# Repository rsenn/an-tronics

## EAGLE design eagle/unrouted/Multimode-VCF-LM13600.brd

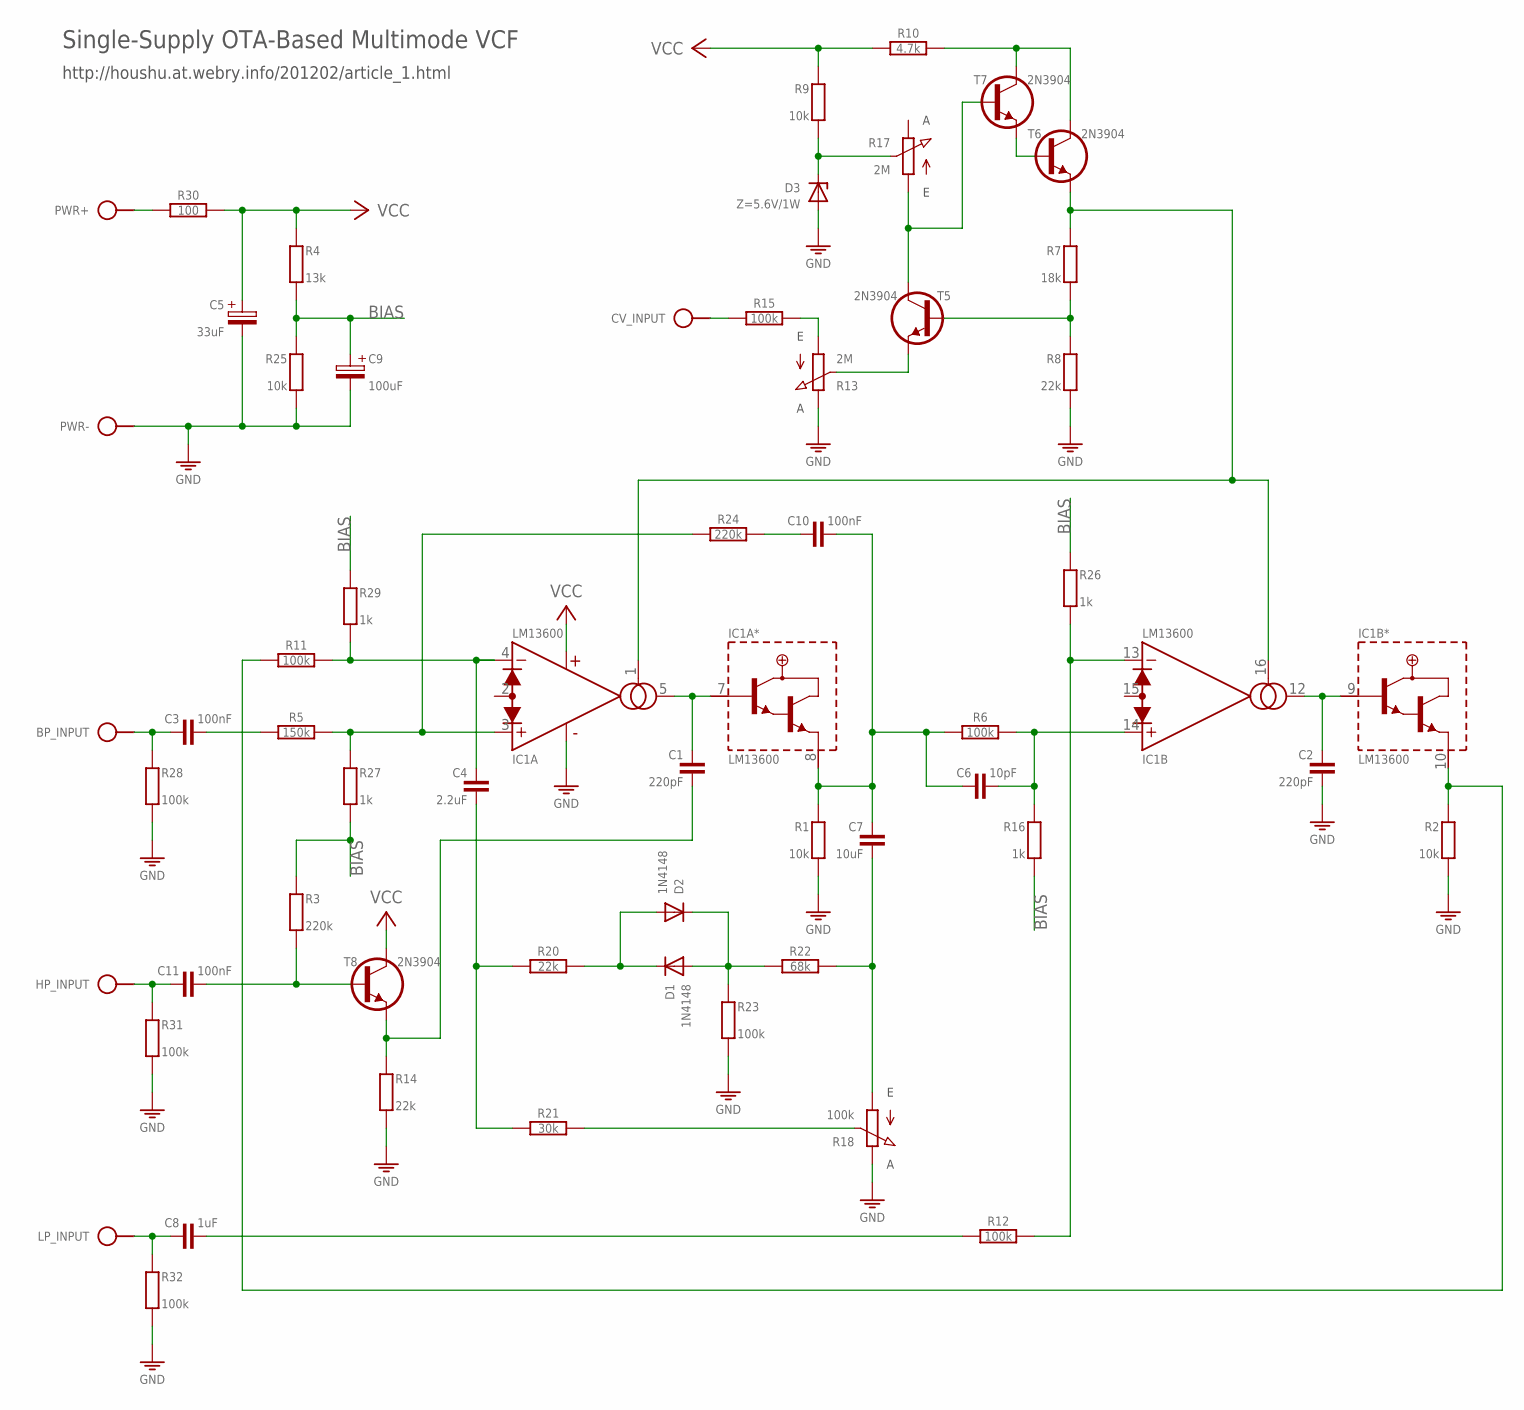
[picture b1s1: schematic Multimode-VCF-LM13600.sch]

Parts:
BP_INPUT: SPAD
C1, C2: 220pF; C050-020X036/V
C3, C10: 100nF; C050-020X044
C4: 2.2uF; C050-024X044/V
C5: 33uF; E2.5-4/V
C6: 10pF; C050-020X036
C7: 10uF; C050-020X036/V
C8: 1uF; C050-024X044
C9: 100uF; E2.5-4/V
C11: 100nF; C050-020X044/V
CV_INPUT: SPAD
D1: 1N4148; DO34-2,5-A
D2: 1N4148; DO34-2,5
D3: Z=5.6V/1W; DO35Z7/V
HP_INPUT: SPAD
IC1: LM13600; DIL16
LP_INPUT: SPAD
PWR: SPAD+--+; SPAD-+
R1, R9, R25: 10k; 0204/10-V
R2: 10k; 0204/10
R3, R24: 220k; 0204/10-V
R4: 13k; 0204/10-V
R5: 150k; 0204/10
R6: 100k; 0204/7-V
R7: 18k; 0204/10-V
R8, R14: 22k; 0204/10-V
R10: 4.7k; 0204/10
R11, R12, R15: 100k; 0204/10
R13, R17: 2M; POT-V
R16: 1k; 0204/7-V
R18: 100k; POT
R20: 22k; 0204/10
R21: 30k; 0204/10
R22: 68k; 0204/10
R23, R28, R31, R32: 100k; 0204/10-V
R26: 1k; 0204/7
R27, R29: 1k; 0204/10-V
R30: 100; 0204/10
T5, T6, T7, T8: 2N3904; TO92

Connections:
BIAS: C9.+, R3.1, R4.2, R16.1 (2), R25.1, R26.2 (1), R27.2, R29.1
GND: C2.2, C5.-, C9.-, D3.A, IC1.6 (V-), PWR.1, R1.2, R2.1 (2), R8.2, R13.E, R14.2, R18.3 (E), R23.2, R25.2, R28.2, R31.2, R32.2
unnamed: C4.2, R20.1, R21.1
unnamed: IC1.3 (+IN), R5.2, R24.1, R27.1
unnamed: C1.2, R14.1, T8.1 (E)
unnamed: C11.2, R3.2, T8.2 (B)
unnamed: C1.1, IC1.5 (OUT), IC1.7 (BUFF/IN)
unnamed: C6.1, C7.1, C10.2, IC1.8 (BUFF/OUT), R1.1, R6.1
unnamed: D1.C, D2.A, R20.2
unnamed: D1.A, D2.C, R22.1, R23.1
unnamed: C10.1, R24.2
unnamed: C6.2, IC1.14 (+IN), R6.2, R16.2 (1)
unnamed: R18.2 (S), R21.2
unnamed: C7.2, R18.1 (A), R22.2
unnamed: C4.1, IC1.4 (-IN), R11.2, R29.2
unnamed: IC1.13 (-IN), R12.2, R26.1 (2)
unnamed: C8.2, R12.1
unnamed: C8.1, LP_INPUT.1, R32.1
unnamed: C11.1, HP_INPUT.1, R31.1
unnamed: C3.2, R5.1
unnamed: BP_INPUT.1, C3.1, R28.1
unnamed: C2.1, IC1.9 (BUFF/IN), IC1.12 (OUT)
unnamed: IC1.10 (BUFF/OUT), R2.2 (1), R11.1
unnamed: R17.A, T5.3 (C), T7.2 (B)
unnamed: T6.2 (B), T7.1 (E)
unnamed: IC1.1 (AMP/BIAS), IC1.16 (AMP/BIAS), R7.1, T6.1 (E)
unnamed: R7.2, R8.1, T5.2 (B)
unnamed: D3.C, R9.2, R17.S
unnamed: R10.2, T6.3 (C), T7.3 (C)
unnamed: R13.S, T5.1 (E)
unnamed: CV_INPUT.1, R15.1
unnamed: R13.A, R15.2
unnamed: PWR.2, R30.1
VCC: C5.+, IC1.11 (V+), R4.1, R9.1, R10.1, R30.2, T8.3 (C)

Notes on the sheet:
http://houshu.at.webry.info/201202/article_1.html
Single-Supply OTA-Based Multimode VCF

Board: 2 copper layers, 55 parts (0 on the bottom side), 34 nets, no tracks yet.

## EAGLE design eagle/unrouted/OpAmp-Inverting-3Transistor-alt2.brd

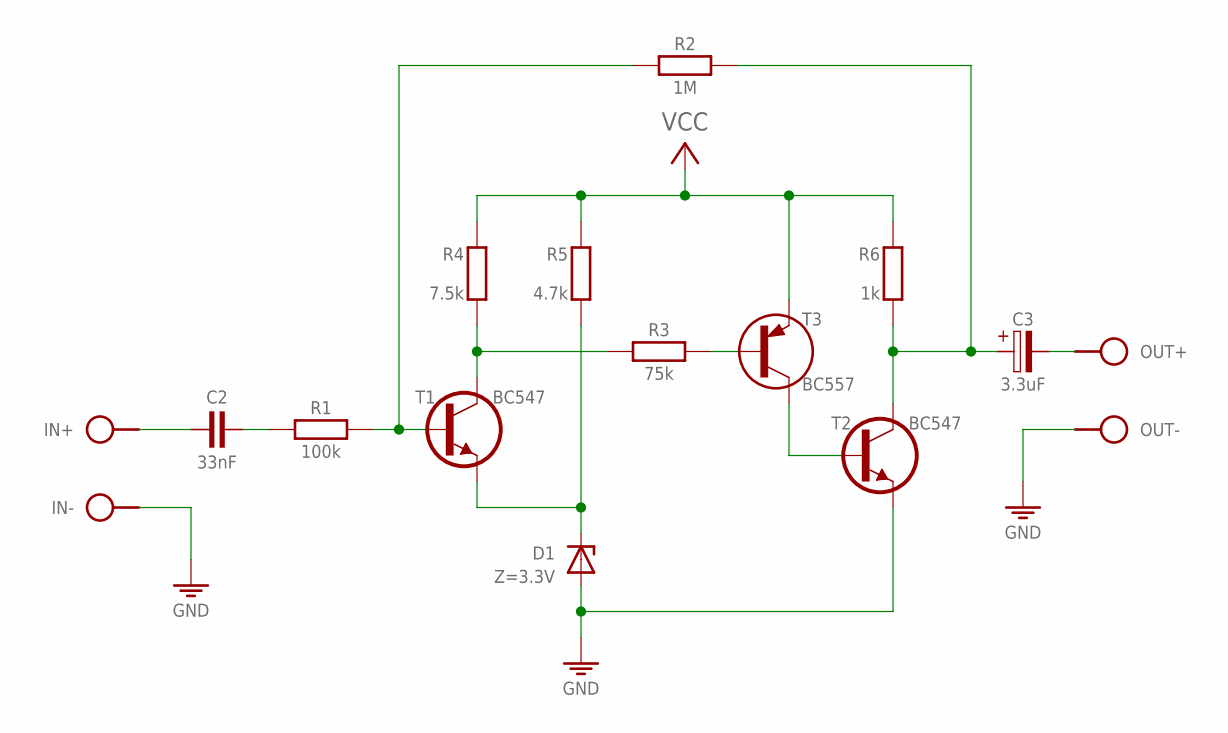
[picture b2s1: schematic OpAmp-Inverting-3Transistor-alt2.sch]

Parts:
C2: 33nF; C050-020X044
C3: 3.3uF; E2.5-4/V
D1: Z=3.3V; DO34Z2,5
IN: SPAD+--+; SPAD-+
J1: VCC_GNDPWR-R; PWR-R
OUT: SPAD+-+-; SPAD+-
R1: 100k; 0202/10-V
R2: 1M; 0202/7
R3: 75k; 0202/7
R4: 7.5k; 0202/7
R5: 4.7k; 0202/7
R6: 1k; 0202/7-V
T1, T2: BC547; TO92-CBE
T3: BC557; TO92-CBE

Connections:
GND: D1.A, IN.1, J1.1 (GND), OUT.1, T2.E
unnamed: D1.C, R5.1 (2), T1.E
unnamed: R3.1, R4.1 (2), T1.C
unnamed: T2.B, T3.C
unnamed: C2.2, IN.2
unnamed: C2.1, R1.1
unnamed: R1.2, R2.1, T1.B
unnamed: R3.2, T3.B
unnamed: C3.+, R2.2, R6.1 (2), T2.C
unnamed: C3.-, OUT.2
VCC: J1.2 (VCC), R4.2 (1), R5.2 (1), R6.2 (1), T3.E

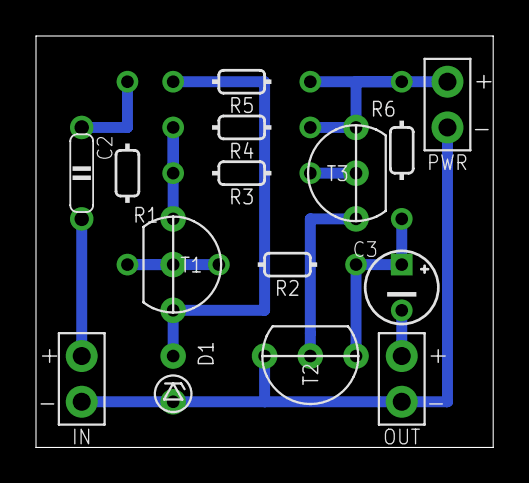
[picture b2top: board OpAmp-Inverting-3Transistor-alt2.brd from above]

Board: 2 copper layers, 25.4 x 22.9 mm, 15 parts (0 on the bottom side), 11 nets.

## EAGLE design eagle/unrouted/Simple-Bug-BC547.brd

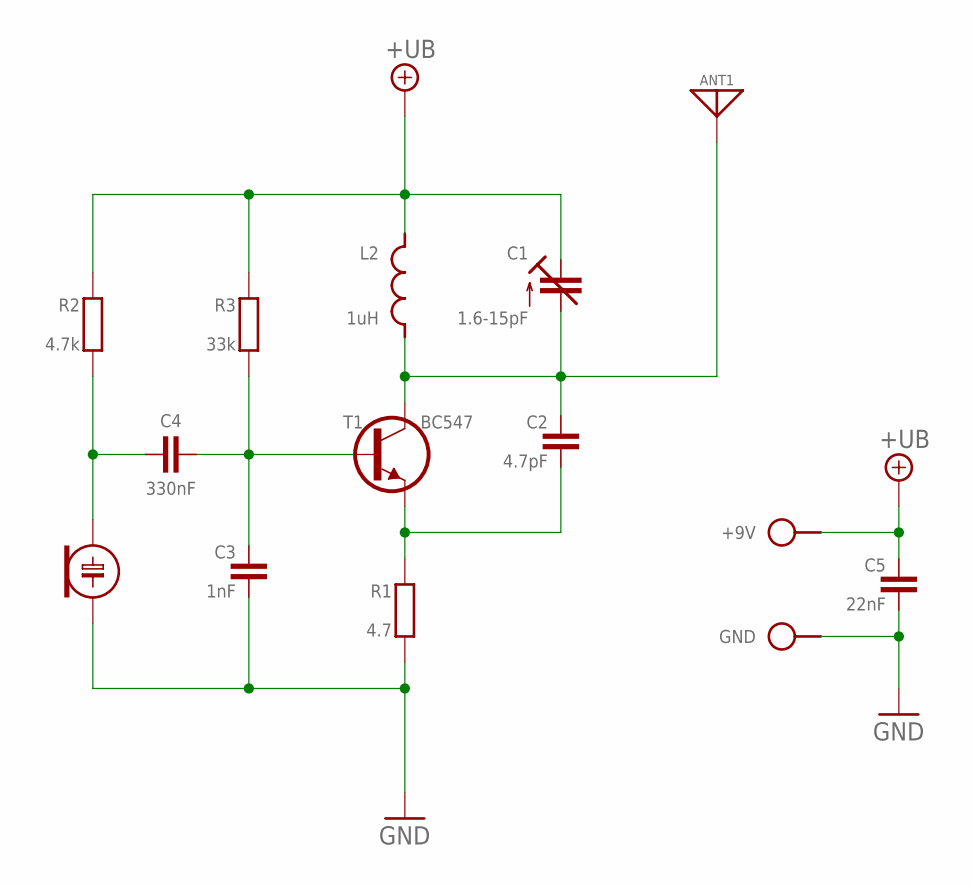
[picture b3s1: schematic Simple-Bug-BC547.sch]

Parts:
+9V: SPAD
ANT1: ANT; SPAD
C1: 1.6-15pF; TRIM-2222-808
C2: 4.7pF; C050-020X036
C3: 1nF; C050-020X036
C4: 330nF; C050-020X044
C5: 22nF; C050-020X036/V
ECM: ECM-4
GND: SPAD
L2: 1uH; L-04/7V-X
R1: 4.7; 0204/7
R2: 4.7k; 0204/7-V
R3: 33k; 0204/7-V
T1: BC547; TO92-CBE

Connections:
+UB: +9V.1, C1.1 (E), C1.3 (E), C5.1, L2.2, R2.1, R3.1
GND: C3.2, C5.2, ECM.2 (-), GND.1, R1.2
unnamed: ANT1.1, C1.2 (A), C2.1, L2.1, T1.C
unnamed: C2.2, R1.1, T1.E
unnamed: C3.1, C4.2, R3.2, T1.B
unnamed: C4.1, ECM.1 (+), R2.2

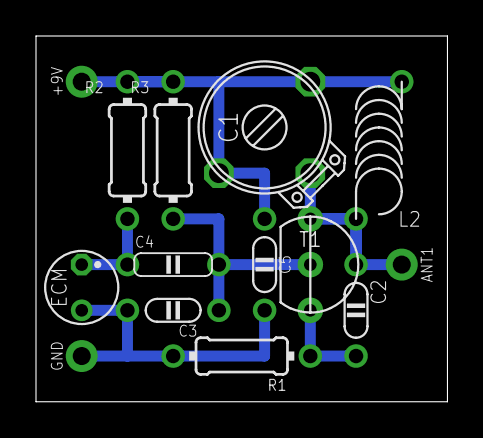
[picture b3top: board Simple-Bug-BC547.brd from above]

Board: 2 copper layers, 22.9 x 20.3 mm, 14 parts (0 on the bottom side), 6 nets.

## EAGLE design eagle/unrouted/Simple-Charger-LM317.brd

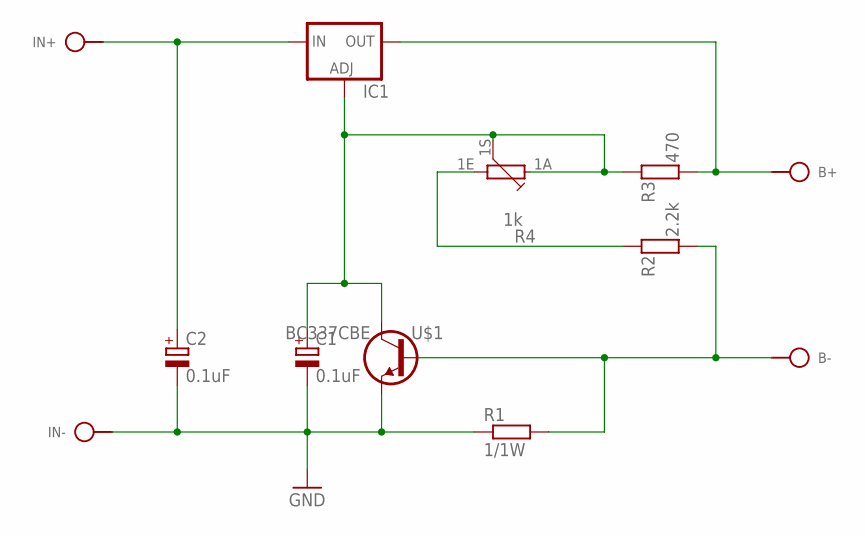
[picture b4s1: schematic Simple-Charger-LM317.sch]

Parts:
B+: SPAD
B-: SPAD
C1: 0.1uF; E5-4
C2: 0.1uF; E2,5-4
IC1: LM317TL; 317TL
IN+: SPAD
IN-: SPAD
R1: 1/1W; 0309/12
R2: 2.2k; 0204/10
R3: 470; 0204/10
R4: 1k; PC16S
U$1: BC337CBE; TO92-CBE

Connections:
GND: C1.-, C2.-, IN-.1, R1.1, U$1.E
unnamed: B-.1, R1.2, R2.1, U$1.B
unnamed: R2.2, R4.1E
unnamed: C1.+, IC1.1 (ADJ), R3.2, R4.1A, R4.1S, U$1.C
unnamed: B+.1, IC1.2 (OUT), R3.1
unnamed: C2.+, IC1.3 (IN), IN+.1

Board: 2 copper layers, 12 parts (0 on the bottom side), 6 nets, no tracks yet.

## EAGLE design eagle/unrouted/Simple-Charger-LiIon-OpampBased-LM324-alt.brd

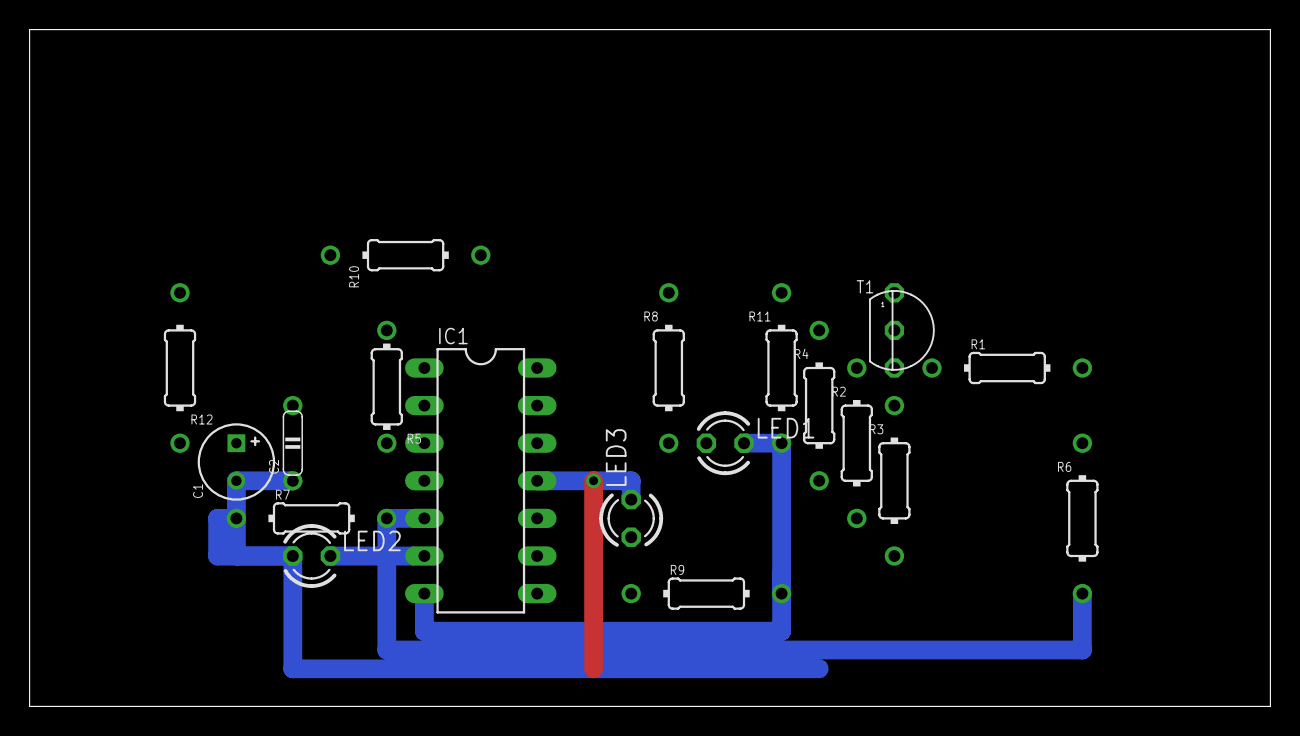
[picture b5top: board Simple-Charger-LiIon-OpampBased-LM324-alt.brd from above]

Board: 2 copper layers, 83.8 x 45.7 mm, 19 parts (0 on the bottom side), 13 nets.

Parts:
C1: 100uF/16V; E2,5-5
C2: 68nF; C050-020X044
IC1: LM324N; DIL14
LED1: Red; LED3MM
LED2: Green; LED3MM
LED3: Blue; LED3MM
R1: 1; 0204/10
R2: 2.7k; 0204/10-V
R3: 2.2k; 0204/10-V
R4: 220; 0204/10-V
R5: 470; 0204/7-V
R6: 4.7k; 0204/10-V
R7: 3.6k; 0204/10
R8: 680; 0204/10-V
R9: 1k; 0204/10
R10: 680k; 0204/10-V
R11: 470; 0204/10-V
R12: 12k; 0204/10-V
T1: BC327; TO92

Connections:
GND: C1.-, C2.1, IC1.11, LED2.A, LED3.K, R7.1
unnamed: IC1.3, R5.1, R12.2
unnamed: IC1.1, R5.2, R8.1, R10.2
unnamed: C2.2, IC1.2, R10.1
unnamed: IC1.6, LED2.K, R3.2
unnamed: LED3.A, R9.1
unnamed: IC1.7, LED1.K, R9.2, R11.2
unnamed: LED1.A, R8.2
unnamed: R4.1, R11.1, T1.2
unnamed: R1.1, R2.2, R3.1, T1.1
unnamed: R1.2, R6.1
unnamed: IC1.5, R6.2, R7.2
V+: C1.+, IC1.4, R2.1, R4.2, R12.1, T1.3

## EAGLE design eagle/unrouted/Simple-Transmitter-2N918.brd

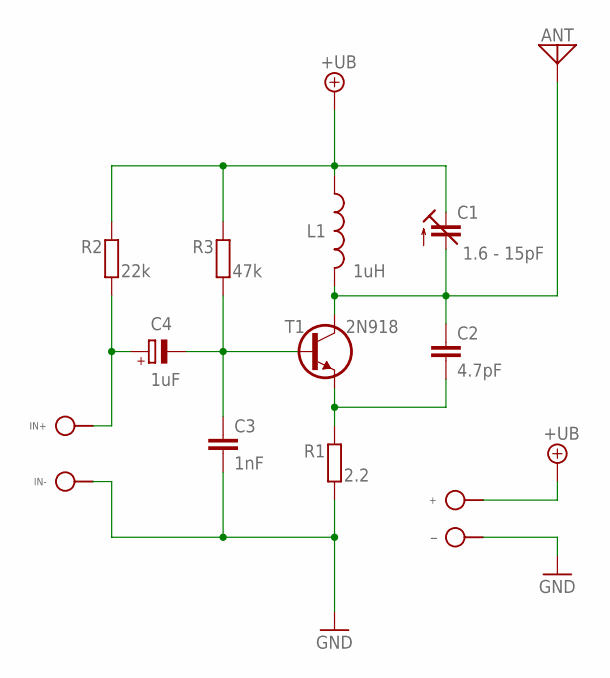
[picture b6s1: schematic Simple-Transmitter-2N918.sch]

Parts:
+: SPAD
ANT: ANT; SPAD
C1: 1.6 - 15pF; TRIM-2222-808
C2: 4.7pF; C025-020X036
C3: 1nF; C025-020X036
C4: 1uF; E2,5-3
IN+: SPAD
IN-: SPAD
L1: 1uH; L-04/7
R1: 2.2; 0202V
R2: 22k; 0202/5
R3: 47k; 0202/5
T1: 2N918; TO-72
̶̶: SPAD

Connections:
+UB: +.1, C1.3 (A), L1.1, R2.2, R3.2
GND: C3.2, IN-.1, R1.1, ̶̶.1
IN+: C4.+, IN+.1, R2.1
unnamed: ANT.1, C1.2 (E), C2.1, L1.2, T1.3 (C)
unnamed: C2.2, R1.2, T1.1 (E), T1.4 (E)
unnamed: C3.1, C4.-, R3.1, T1.2 (B)

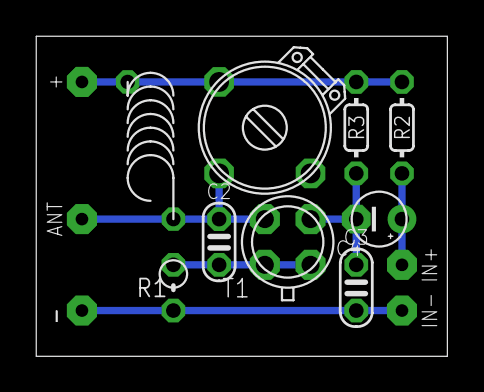
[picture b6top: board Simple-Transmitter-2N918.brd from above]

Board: 2 copper layers, 22.8 x 17.8 mm, 14 parts (0 on the bottom side), 6 nets.

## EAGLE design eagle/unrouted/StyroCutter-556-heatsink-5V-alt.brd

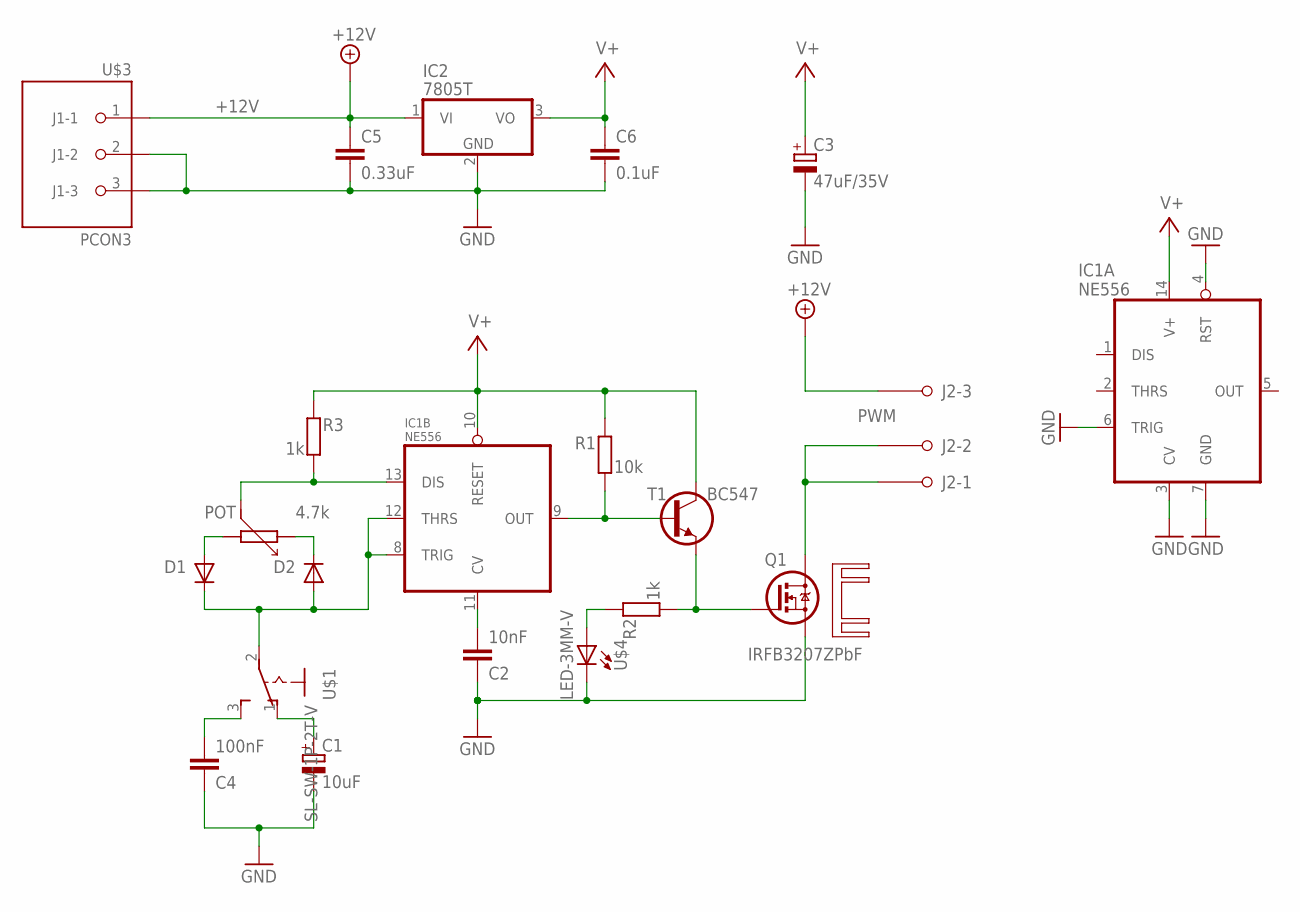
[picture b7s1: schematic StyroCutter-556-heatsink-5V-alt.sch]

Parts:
C1: 10uF; E5-4
C2: 10nF; C075-032X103
C3: 47uF/35V; E2,5-5
C4: 100nF; C050-020X036
C5: 0.33uF; C050-024X044
C6: 0.1uF; C050-025X075
D1, D2: 1N4148; DO34-5
IC1: NE556; DIL14
IC2: 7805T; TO220H
J2: PCON3_MIGROS; CON-MIGROS-3PIN
POT: 4.7k; PC16S
Q1: IRFB3207ZPbF; TO220BV
R1: 10k; 0204/12
R2: 1k; 0204/10
R3: 1k; 0202/2V
T1: BC547; TO92-CBE
U$1: SL-SW-1P-2T-V; SLSW-1P2T-V
U$2: AQ; AQ_HS_3A
U$3: PCON3; CON-MIGROS-3PIN
U$4: LED-3MM-V

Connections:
+12V: C5.1, IC2.1 (VI), J2.3, U$3.1 (J1-1)
GND: C1.-, C2.1, C3.-, C4.1, C5.2, C6.2, IC1.3 (CV), IC1.4 (RST), IC1.6 (TRIG), IC1.7 (GND), IC2.2 (GND), Q1.S, U$3.2 (J1-2), U$3.3 (J1-3), U$4.C
unnamed: D2.C, POT.1A
unnamed: D1.A, POT.1E
unnamed: IC1.9 (OUT), R1.1, T1.B
unnamed: C4.2, U$1.3 (S)
unnamed: C2.2, IC1.11 (CV)
unnamed: IC1.13 (DIS), POT.1S, R3.1
unnamed: Q1.G, R2.1, T1.E
unnamed: D1.C, D2.A, IC1.8 (TRIG), IC1.12 (THRS), U$1.2
unnamed: C1.+, U$1.1 (O)
unnamed: R2.2, U$4.A
PWM: J2.1, J2.2, Q1.D
V+: C3.+, C6.1, IC1.10 (RESET), IC1.14 (V+), IC2.3 (VO), R1.2, R3.2, T1.C

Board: 2 copper layers, 21 parts (1 on the bottom side), 14 nets, no tracks yet.
